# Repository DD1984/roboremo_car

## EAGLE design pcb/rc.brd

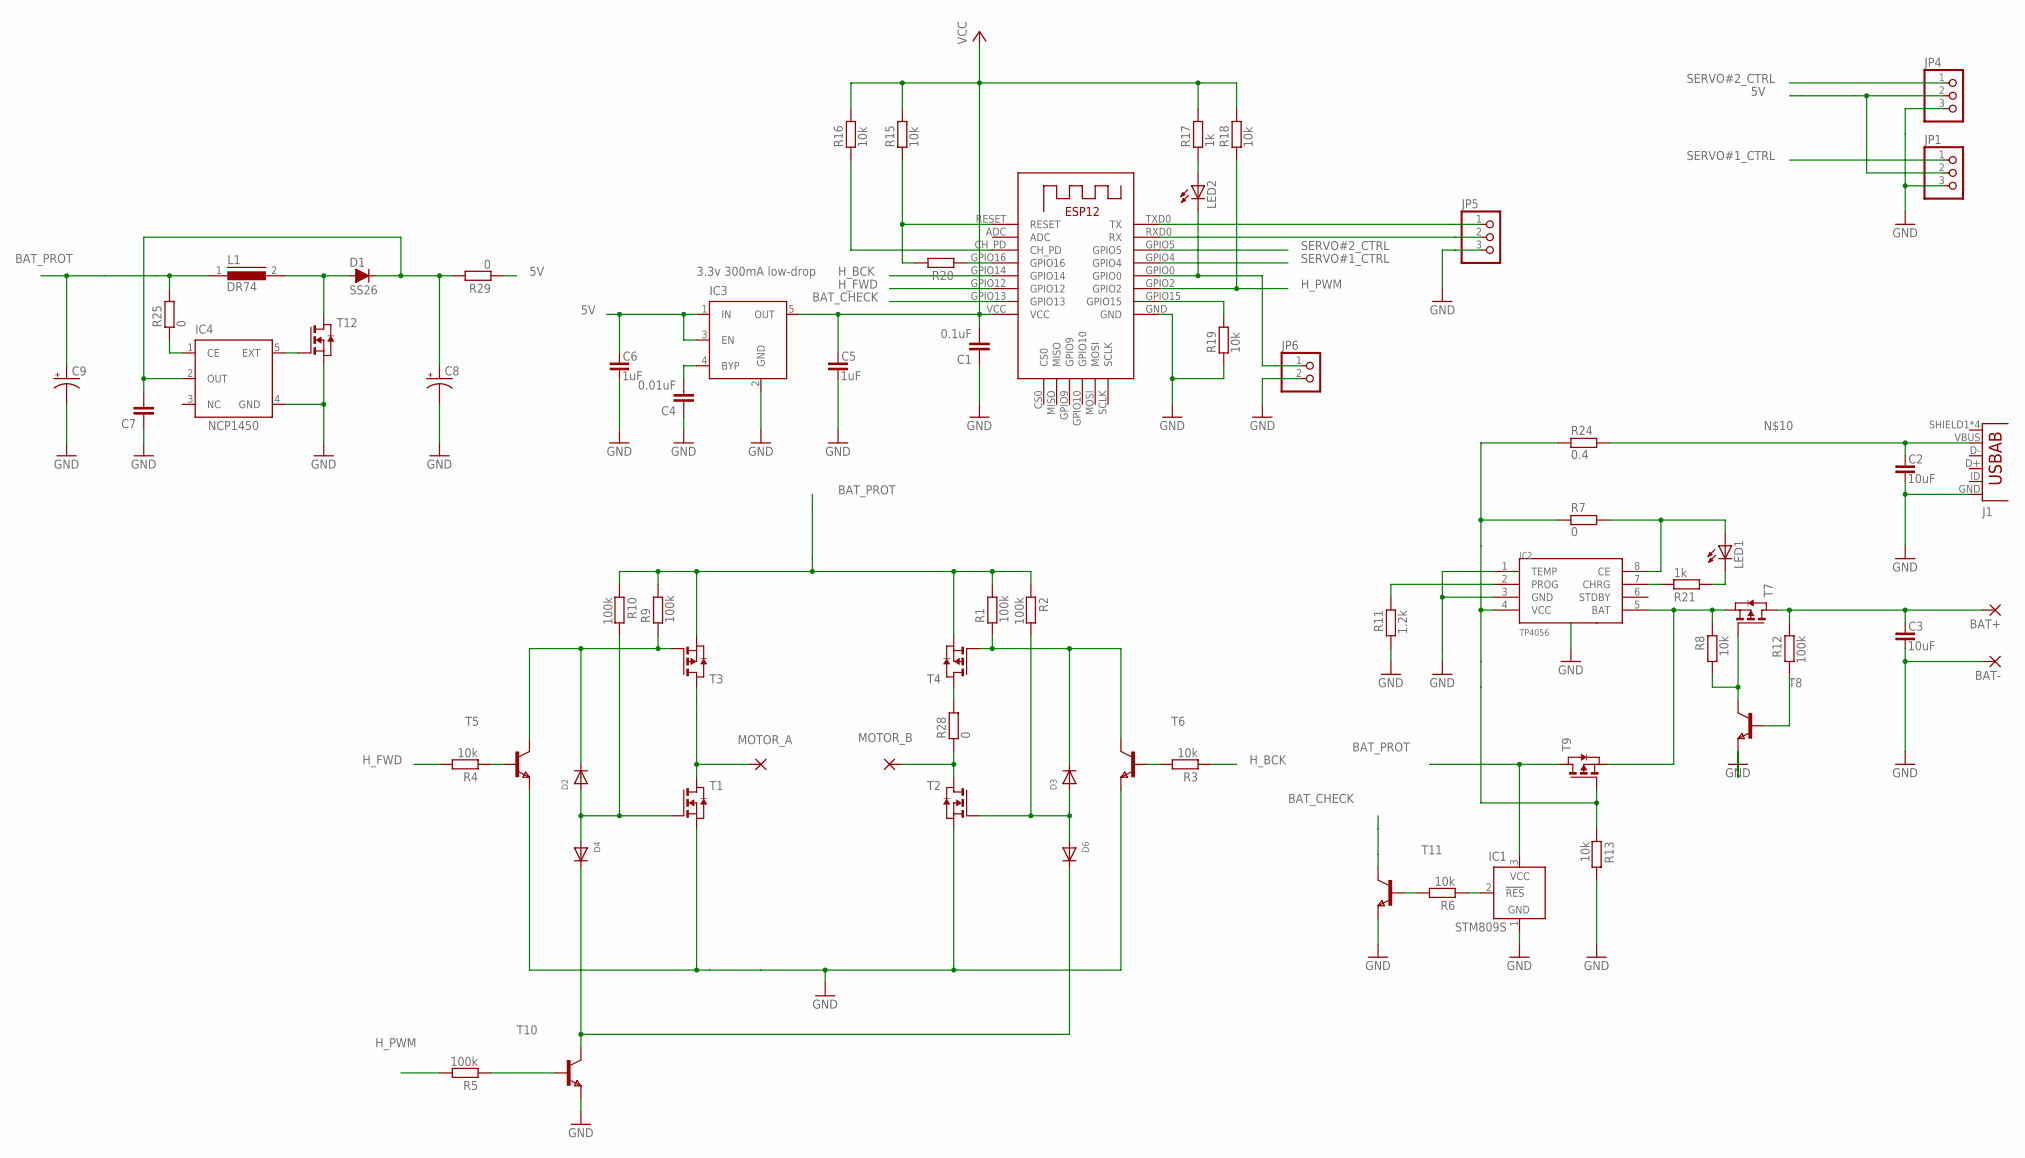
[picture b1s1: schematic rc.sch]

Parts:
BAT+: WIREPADSMD5-2,5; 5-2,5
BAT-: WIREPADSMD5-2,5; 5-2,5
C1: 0.1uF; C0805
C2, C3: 10uF; C1206
C4: 0.01uF; C0805
C5, C6: 1uF; C0805
C7: C-EUC0805; C0805
C8, C9: CPOL-USCT6032; CT6032
D1: SS26; SMB
D2, D3, D4, D6: DIODE_SOD-123FL; SOD-123FL
IC1: STM809S; SOT23B-3
IC2: TP4056; SOP-8
IC3: 3.3v 300mA low-drop; SOT23-5
IC4: NCP1450; SOT23-5
J1: USB-AB; USB-AB-MICRO-SMD
JP1, JP4, JP5: PINHD-1X3; 1X03
JP6: PINHD-1X2; 1X02
L1: DR74
LED1, LED2: LEDCHIPLED_0805; CHIPLED_0805
MOTOR_A: WIREPADSMD5-2,5; 5-2,5
MOTOR_B: WIREPADSMD5-2,5; 5-2,5
R1, R2, R5, R9, R10, R12: 100k; R0805
R3, R4, R6, R8, R13, R15, R16, R18, R19: 10k; R0805
R7, R25, R28, R29: 0; R1206
R11: 1.2k; R0805
R17, R21: 1k; R0805
R20: R_0805; R0805
R24: 0.4; R1206
T1, T2, T12: NMOSSOT23; SOT-23
T3, T4, T7, T9: PMOSSOT23; SOT-23
T5, T6, T8, T10, T11: NPNSOT23; SOT-23
U1: ESP-12

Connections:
5V: C6.1, IC3.1 (IN), IC3.3 (EN), JP1.2, JP4.2, R29.1
BAT+: BAT+.1, C3.1, R12.1, T7.1 (D)
BAT_CHECK: T11.1 (C), U1.GPIO13
BAT_CHRG: IC2.5 (BAT), R8.1, T7.2 (S), T9.2 (S)
BAT_PROT: C9.+, IC1.3 (VCC), L1.1, R1.2, R2.1, R9.2, R10.1, R25.2, T3.2 (S), T4.2 (S), T9.1 (D)
GND: BAT-.1, C1.1, C2.2, C3.2, C4.1, C5.2, C6.2, C7.1, C8.-, C9.-, IC1.1 (GND), IC2.1 (TEMP), IC2.3 (GND), IC2.HEATSINK, IC3.2 (GND), IC4.4 (GND), J1.GND, JP1.3, JP4.3, JP5.3, JP6.2, R11.2, R13.2, R19.1, T1.2 (S), T2.2 (S), T5.2 (E), T6.2 (E), T8.2 (E), T10.2 (E), T11.2 (E), T12.2 (S), U1.GND
H_BCK: R3.1, U1.GPIO14
H_FWD: R4.2, U1.GPIO12
H_PWM: R5.2, R18.1, U1.GPIO2
unnamed: D2.C, R9.1, T3.3 (G), T5.1 (C)
unnamed: IC2.8 (CE), LED1.A, R7.2
unnamed: D1.2 (A), L1.2, T12.1 (D)
unnamed: MOTOR_B.1, R28.1, T2.1 (D)
unnamed: R4.1, T5.3 (B)
unnamed: D2.A, D4.A, R10.2, T1.3 (G)
unnamed: R3.2, T6.3 (B)
unnamed: D3.C, R1.1, T4.3 (G), T6.1 (C)
unnamed: D3.A, D6.A, R2.2, T2.3 (G)
unnamed: C2.1, J1.VBUS, R24.2
unnamed: IC2.2 (PROG), R11.1
unnamed: R8.2, T7.3 (G), T8.1 (C)
unnamed: R6.2, T11.3 (B)
unnamed: R28.2, T4.1 (D)
unnamed: IC4.5 (EXT), T12.3 (G)
unnamed: R12.2, T8.3 (B)
unnamed: IC1.2 (!RES), R6.1
unnamed: IC4.1 (CE), R25.1
unnamed: R15.1, R20.2, U1.RESET
unnamed: R16.1, U1.CH_PD
unnamed: JP6.1, LED2.C, U1.GPIO0
unnamed: R20.1, U1.GPIO16
unnamed: LED2.A, R17.1
unnamed: C4.2, IC3.4 (BYP)
unnamed: R19.2, U1.GPIO15
unnamed: LED1.C, R21.2
unnamed: IC2.7 (CHRG), R21.1
unnamed: C7.2, C8.+, D1.1 (C), IC4.2 (OUT), R29.2
unnamed: D4.C, D6.C, T10.1 (C)
unnamed: R5.1, T10.3 (B)
unnamed: MOTOR_A.1, T1.1 (D), T3.1 (D)
RX: JP5.2, U1.RXD0 (RX)
SERVO#1_CTRL: JP1.1, U1.GPIO4
SERVO#2_CTRL: JP4.1, U1.GPIO5
TX: JP5.1, U1.TXD0 (TX)
VCC: C1.2, C5.1, IC3.5 (OUT), R15.2, R16.2, R17.2, R18.2, U1.VCC
V_CHRG: IC2.4 (VCC), R7.1, R13.1, R24.1, T9.3 (G)

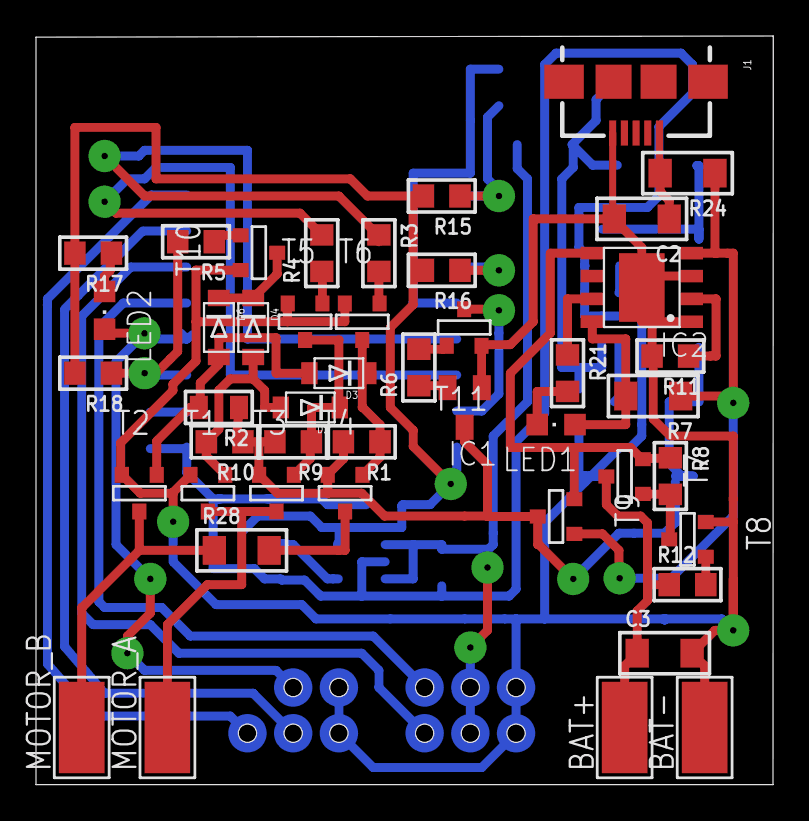
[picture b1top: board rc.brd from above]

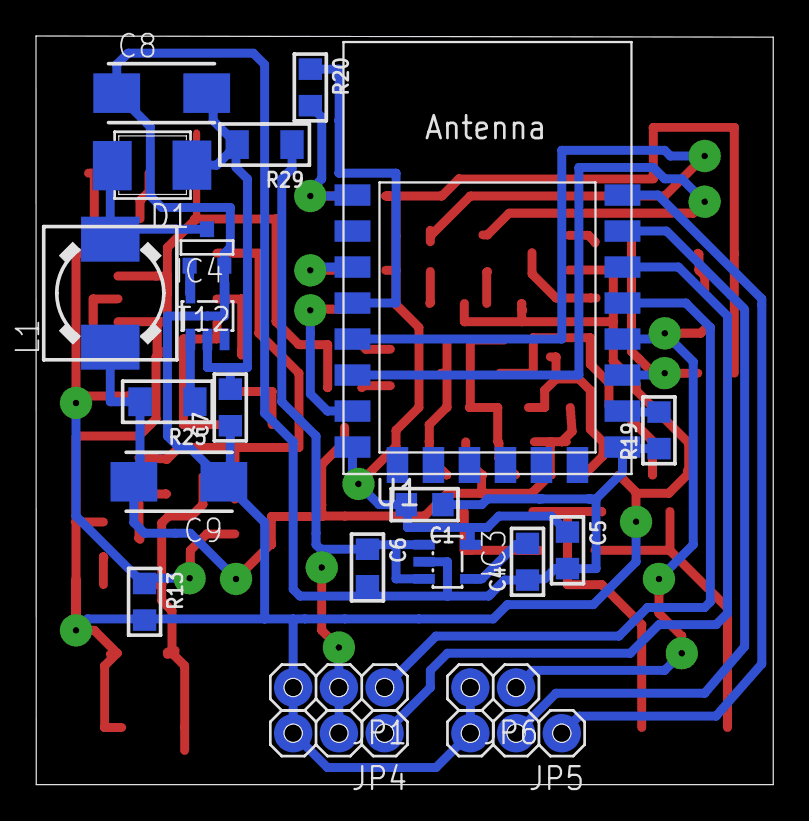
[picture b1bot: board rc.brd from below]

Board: 2 copper layers, 41.0 x 41.6 mm, 67 parts (22 on the bottom side), 46 nets.

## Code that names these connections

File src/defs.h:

#ifndef __DEFS_H__
#define __DEFS_H__

#define WIFI_SSID "mywifi"
#define WIFI_PSK ""
#define WIFI_CHANNEL 1

#define PORT 9876

#define CON_CHECK_INTERVAL 500 //ms

#define SPEED_EXPO 55

// H-bridge gpios
#define H_BCK_PIN 14
#define H_FWD_PIN 12
#define H_PWM_PIN 2

#define AUTO_BRAKE //brake motor when motor channel == 0

#define BAT_CHECK_PIN 13
#define BAT_CHECK_INTERVAL 100 //ms
#define BAT_CHECK_MAX_CNT  10

#define SERVO_PINS {4, 5}
#define SERVO_EXPO {55, 0}

#define LED_PIN 0

#define ARRAY_SIZE(x) (sizeof(x) / sizeof(x[0]))

#endif

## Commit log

2018-09-20 add src
2018-09-20 add pcb
2018-09-21 add connection checking
2018-09-23 many improvment in fw
2018-09-24 break sources into several files
2018-09-25 add led api
2018-09-25 move led ctrl from loop() to ticker
2018-09-25 bat check move to ticker and to separate file
2018-09-25 con check implement as fsm and move to separate file
2018-09-25 remove int16_t servo_val
2018-09-28 scheme: change H-bridge and battety check
2018-09-30 fsm to new file, new state - BAT_LOW
2018-10-02 add servo trimmer
2018-10-02 change trim function from 2 buttons to one slider for save roboremo ctrls
2018-10-08 begin pcb v2
2018-10-21 pcb 0.5mm
2018-10-22 piout for new pcb
2018-10-22 add values for some components
2018-10-23 auto_brake function
2018-10-28 multi servos
2019-10-30 add photo
